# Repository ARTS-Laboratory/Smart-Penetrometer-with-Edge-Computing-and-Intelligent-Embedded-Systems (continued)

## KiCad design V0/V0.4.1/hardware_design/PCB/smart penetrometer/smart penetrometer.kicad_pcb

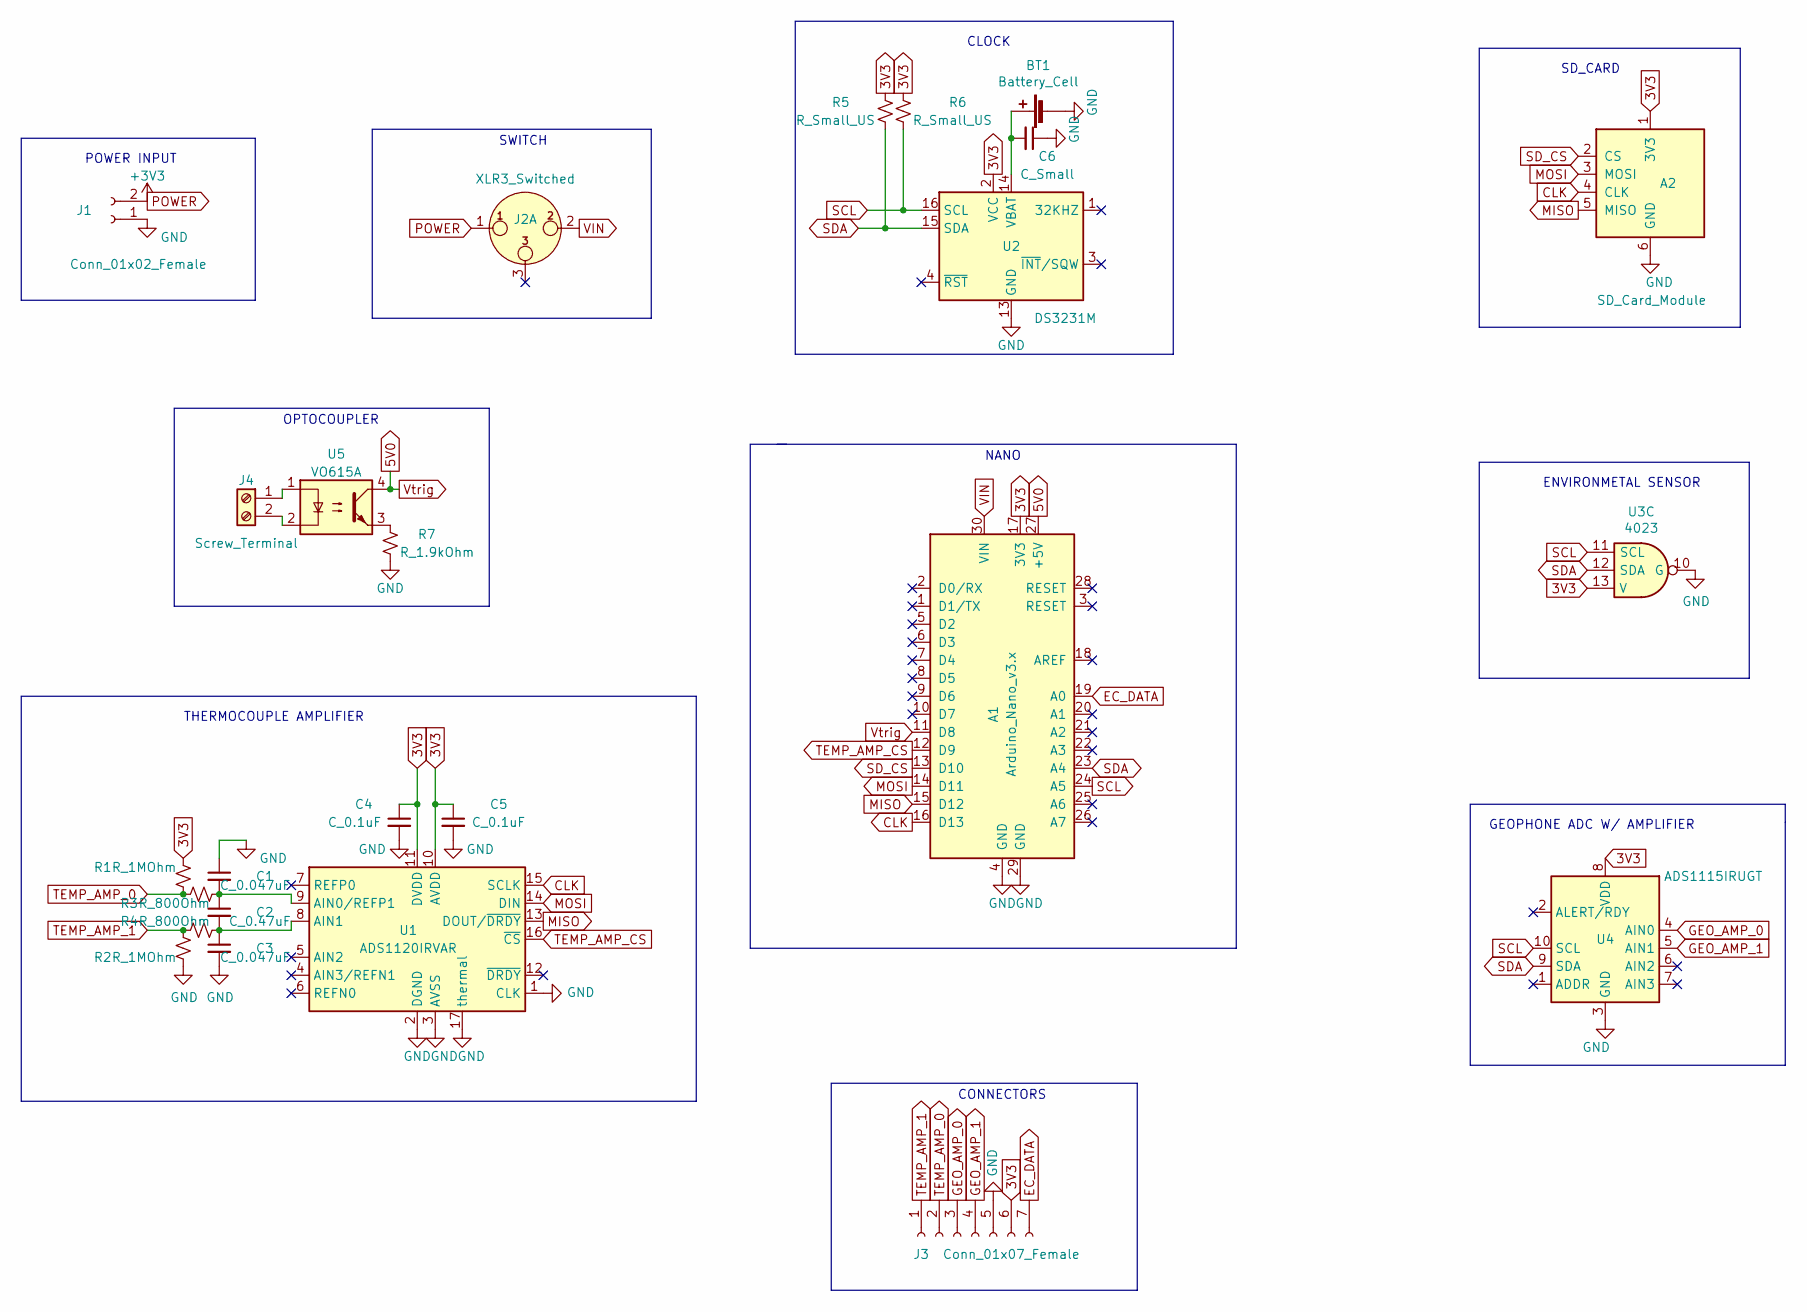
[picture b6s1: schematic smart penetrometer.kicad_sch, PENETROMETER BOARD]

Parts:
A1: Arduino_Nano_v3.x; Arduino_Nano
A2: SD_Card_Module; SD Module
BT1: Battery_Cell; battery_holder_10mm
C1, C3: C_0.047uF; C_1206_3216Metric
C2: C_0.47uF; C_1206_3216Metric
C4, C5: C_0.1uF; C_1206_3216Metric
C6: C_Small; C_1206_3216Metric
J1: Conn_01x02_Female; PinSocket_1x02_P2.54mm_Horizontal
J2: XLR3_Switched; grounded_switch
J3: Conn_01x07_Female; PinSocket_1x07_P2.54mm_Horizontal
J4: Screw_Terminal; TerminalBlock_bornier-2_P5.08mm
R1, R2: R_1MOhm; R_1206_3216Metric
R3, R4: R_800Ohm; R_1206_3216Metric
R5, R6: R_Small_US; R_1206_3216Metric
R7: R_1.9kOhm; R_1206_3216Metric
U1: ADS1120IRVAR; VQFN-16-1EP_3x3mm_P0.5mm_EP1.45x1.45mm_ThermalVias
U2: DS3231M; SOIC-16W_7.5x10.3mm_P1.27mm
U3: 4023; TDS_module
U4: ADS1115IRUGT; 10X2QFN
U5: VO615A; Vishay_VOS615A

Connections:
3V3: A1.17 (3V3), A2.1 (3V3), C4.1, C5.1, J3.6, R1.1, R5.1, R6.1, U1.10 (AVDD), U1.11 (DVDD), U2.2 (VCC), U3.13, U4.8 (VDD)
5V0: A1.11 (D8), A1.27 (+5V), U5.4
CLK: A1.16 (D13), A2.4 (CLK), U1.15 (SCLK)
EC_DATA: A1.19 (A0), J3.7
GEO_AMP_0: J3.3, U4.4 (AIN0)
GEO_AMP_1: J3.4, U4.5 (AIN1)
GND: A1.4 (GND), A1.29 (GND), A2.6 (GND), BT1.2 (-), C1.1, C3.2, C4.2, C5.2, C6.1, J1.1, J3.5, R2.2, R7.2, U1.1 (CLK), U1.2 (DGND), U1.3 (AVSS), U1.17 (thermal), U2.5 (GND), U2.6 (GND), U2.7 (GND), U2.8 (GND), U2.9 (GND), U2.10 (GND), U2.11 (GND), U2.12 (GND), U2.13 (GND), U3.10, U4.3 (GND)
MISO: A1.15 (D12), A2.5 (MISO), U1.13 (DOUT/~DRDY)
MOSI: A1.14 (D11), A2.3 (MOSI), U1.14 (DIN)
unnamed: BT1.1 (+), C6.2, U2.14 (VBAT)
unnamed: C1.2, C2.1, R3.1, U1.9 (AIN0/REFP1)
unnamed: C2.2, C3.1, R4.1, U1.8 (AIN1)
unnamed: J4.1, U5.1
unnamed: J4.2, U5.2
unnamed: R7.1, U5.3
POWER: J1.2, J2.1
SCL: A1.24 (A5), R6.2, U2.16 (SCL), U3.11, U4.10 (SCL)
SDA: A1.23 (A4), R5.2, U2.15 (SDA), U3.12, U4.9 (SDA)
SD_CS: A1.13 (D10), A2.2 (CS)
TEMP_AMP_0: J3.2, R1.2, R3.2
TEMP_AMP_1: J3.1, R2.1, R4.2
TEMP_AMP_CS: A1.12 (D9), U1.16 (~CS)
VIN: A1.30 (VIN), J2.2

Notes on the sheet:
THERMOCOUPLE AMPLIFIER
POWER INPUT
NANO
SWITCH
CLOCK
CONNECTORS
SD_CARD
ENVIRONMETAL SENSOR
GEOPHONE ADC W/ AMPLIFIER
OPTOCOUPLER

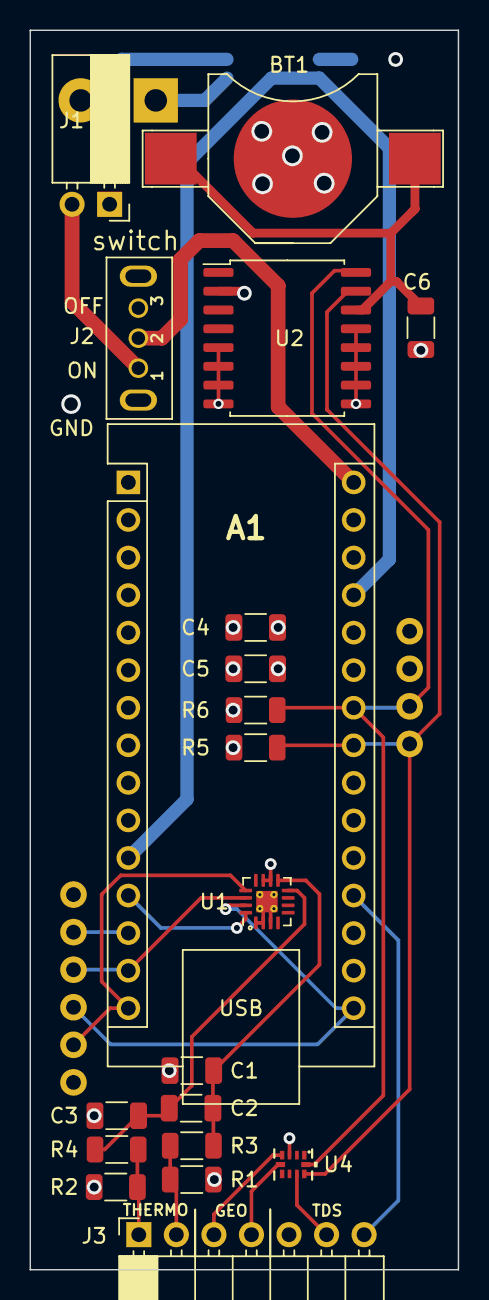
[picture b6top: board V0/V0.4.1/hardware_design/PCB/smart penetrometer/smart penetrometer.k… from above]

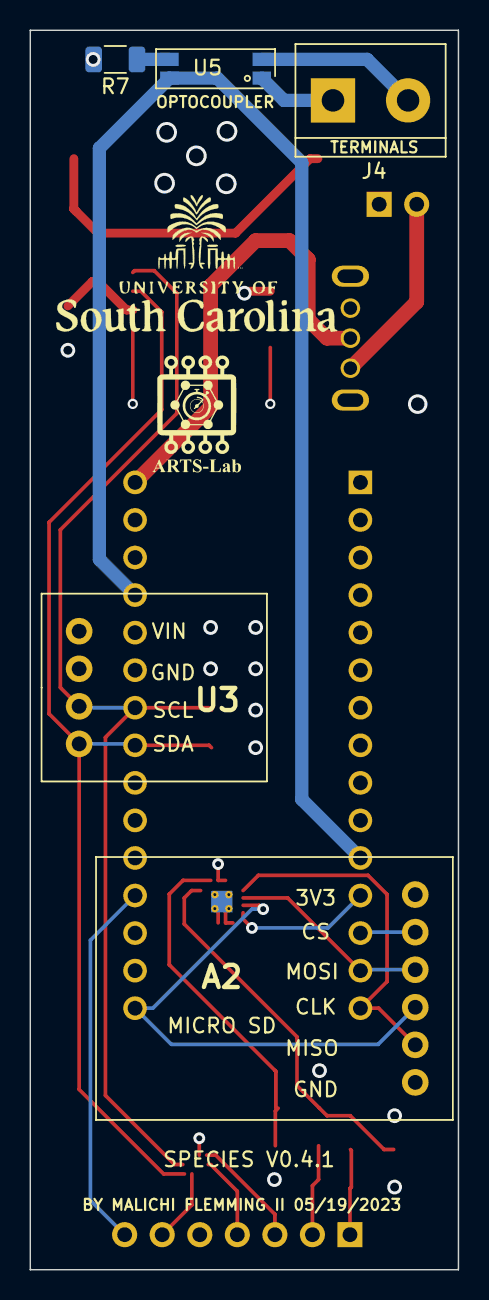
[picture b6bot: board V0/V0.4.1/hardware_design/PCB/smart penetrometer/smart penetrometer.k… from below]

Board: 4 copper layers, 29.0 x 83.8 mm, 25 parts (5 on the bottom side), 23 nets.

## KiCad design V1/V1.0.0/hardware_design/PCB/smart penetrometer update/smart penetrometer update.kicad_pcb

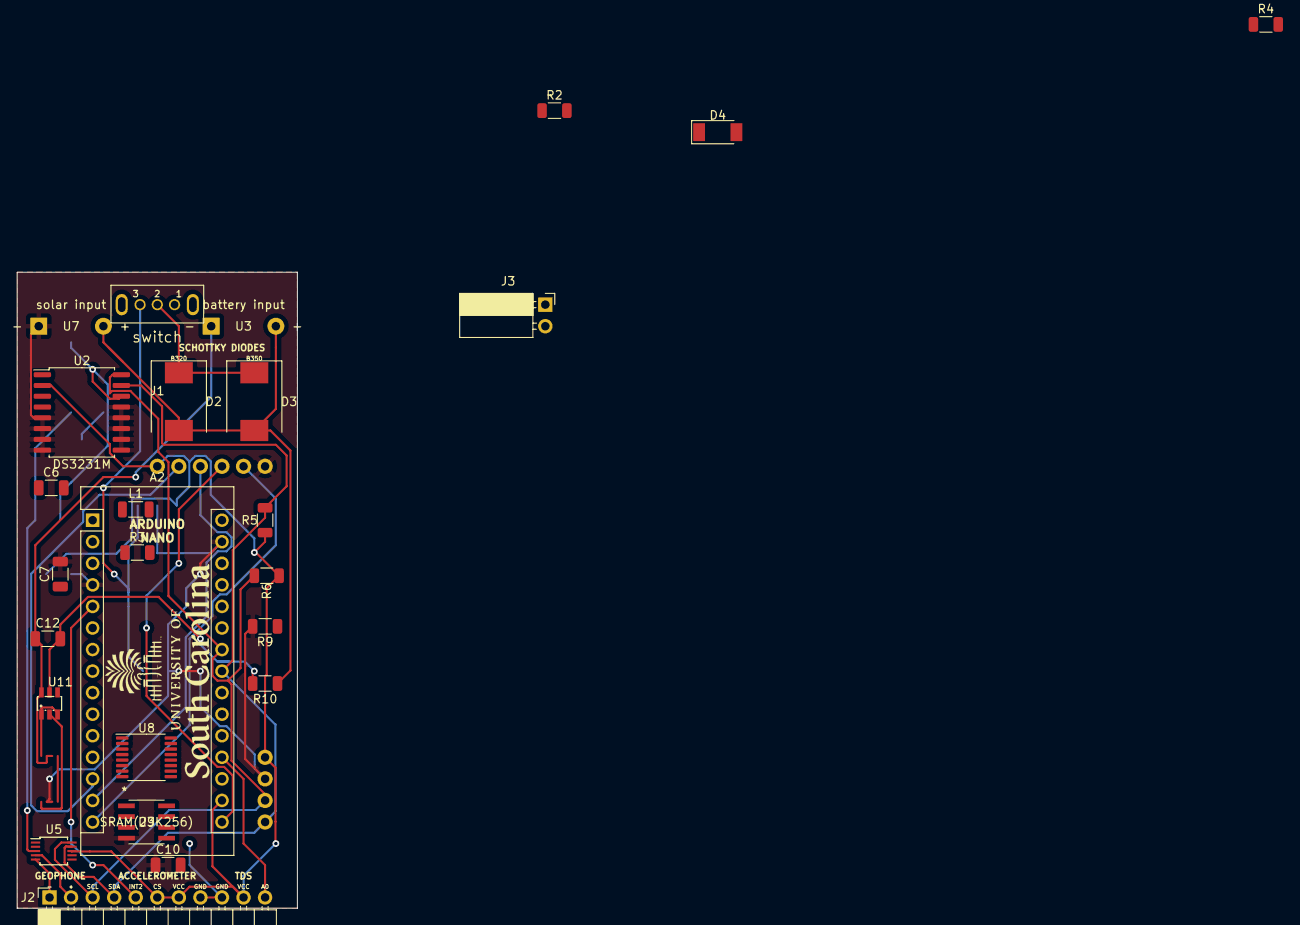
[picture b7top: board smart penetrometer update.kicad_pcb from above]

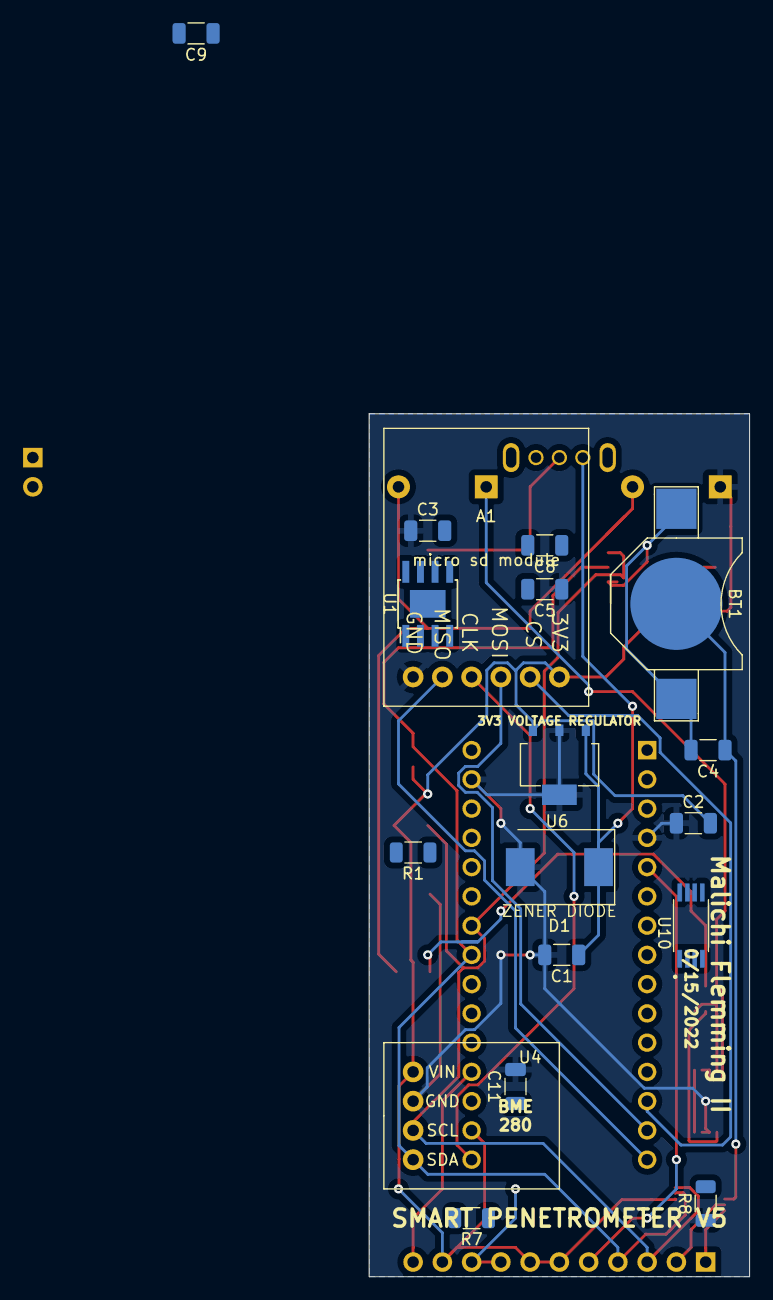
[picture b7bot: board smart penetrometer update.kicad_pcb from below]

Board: 2 copper layers, 33.0 x 74.9 mm, 45 parts (18 on the bottom side), 35 nets.

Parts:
A1: SD_Card_Module; SD Module
A2: Arduino_Nano_v3.x; Arduino_Nano
BT1: Battery_Cell; battery_holder_10mm
C1, C9, C10, C11: C_0.1uF; C_1206_3216Metric
C2, C3, C8: C_10uF; C_1206_3216Metric
C4: C_Small; C_1206_3216Metric
C5, C7: C_0.047uF; C_1206_3216Metric
C6: C_0.47uF; C_1206_3216Metric
C12: CP1_Small; C_1206_3216Metric
D1: D_Zener_Small; D_SMC
D2: B320; D_SMC
D3: B350; D_SMC
D4: PMEG6045ETP; D_SOD-128
J1: XLR3_Switched; grounded_switch
J2: Conn_01x11_Female; PinSocket_1x11_P2.54mm_Horizontal
J3: Conn_01x02_Female; PinSocket_1x02_P2.54mm_Horizontal
L1: L; L_1206_3216Metric
R1, R2: R_1MOhm; R_1206_3216Metric
R3, R4: R_800Ohm; R_1206_3216Metric
R5, R6, R7, R8, R9, R10: R_Small_US; R_1206_3216Metric
U1: 4001; uofsc_logo_1in
U1#2: LM22676MR-5; TI_SO-PowerPAD-8
U2: DS3231M; SOIC-16W_7.5x10.3mm_P1.27mm
U3: Battery_Input
U4: 4023; TDS_module
U5: ADS1115IDGS; TSSOP-10_3x3mm_P0.5mm
U6: 3v3_Voltage_Regulator; BD433M2FP3_CE2
U7: Solar_Input; Battery_Input
U8: ADS1120-PW; TSSOP-16_4.4x5mm_P0.65mm
U9: SRAM(23K256); 23K256T-E&slash_SN
U10: FS8205A; DUAL_MOSFET(FS8205A)
U11: DW01; BATTERY_PROTECTION_IC(DW01A)

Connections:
+BATT: D2.2, D3.2, R10.1, U3.1, U7.1
-BATT: C12.1, U3.2, U10.2, U10.3, U11.6
GND: A1.6, A2.4, A2.29, C1.2, C2.1, C3.1, C5.1, C7.2, C9.2, C10.1, C11.2, D1.2, D4.2, R2.2, R8.1, R9.2, U1#2.6, U2.5, U2.6, U2.7, U2.8, U2.9, U2.10, U2.11, U2.12, U2.13, U4.10, U6.2, U6.4, U7.2, U8.3, U8.5, U9.4, U10.6, U10.7
GNDREF: J2.8, J2.9
GNDS: BT1.2, C4.1, U5.3
unnamed: A1.1, A2.30, C2.2, C9.1, C11.1, J2.6, J2.7, J2.10, R1.1, R5.1, R6.1, U2.2, U4.13, U5.8, U6.3, U8.12, U8.13, U9.8
unnamed: A1.2, A2.13
unnamed: A1.3, A2.14, U8.16, U9.5
unnamed: A1.4, A2.16, U8.1, U9.6
unnamed: A1.5, A2.15, U8.15, U9.2
unnamed: A2.5, J2.5
unnamed: A2.10, U9.7
unnamed: A2.11, U9.1
unnamed: A2.12, U8.2
unnamed: A2.19, J2.11
unnamed: A2.23, J2.4, R5.2, U2.15, U4.12, U5.9
unnamed: A2.24, J2.3, R6.2, U2.16, U4.11, U5.10
unnamed: BT1.1, C4.2, U2.14
unnamed: C1.1, C10.2, D1.1, L1.1, R7.1, U6.1
unnamed: C3.2, J1.3, U1#2.7
unnamed: C5.2, C6.1, R3.1, U8.11
unnamed: C6.2, C7.1, R4.1, U8.10
unnamed: C8.1, D4.1, L1.2, U1#2.8
unnamed: C8.2, U1#2.1
unnamed: C12.2, R10.2, U11.5
unnamed: D2.1, D3.1, J1.2
unnamed: J2.1, U5.5
unnamed: J2.2, U5.4
unnamed: J3.1, R2.1, R4.2
unnamed: J3.2, R1.2, R3.2
unnamed: R7.2, R8.2, U1#2.4
unnamed: R9.1, U11.2
unnamed: U10.1, U10.8
unnamed: U10.4, U11.1
unnamed: U10.5, U11.3

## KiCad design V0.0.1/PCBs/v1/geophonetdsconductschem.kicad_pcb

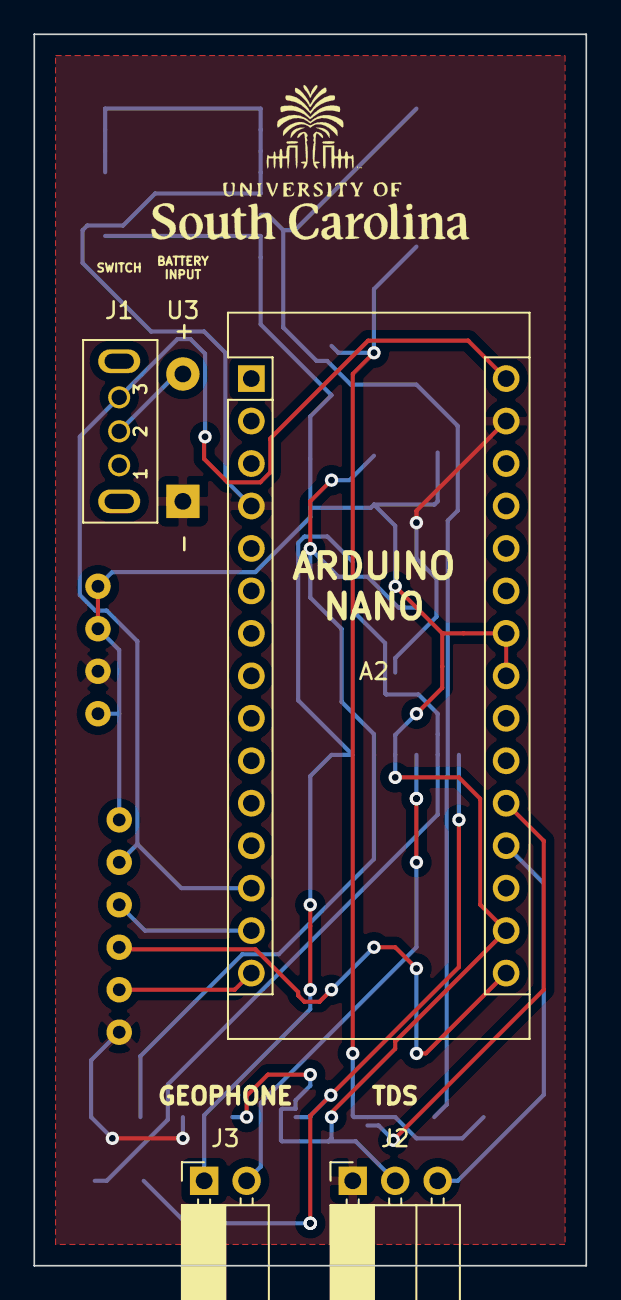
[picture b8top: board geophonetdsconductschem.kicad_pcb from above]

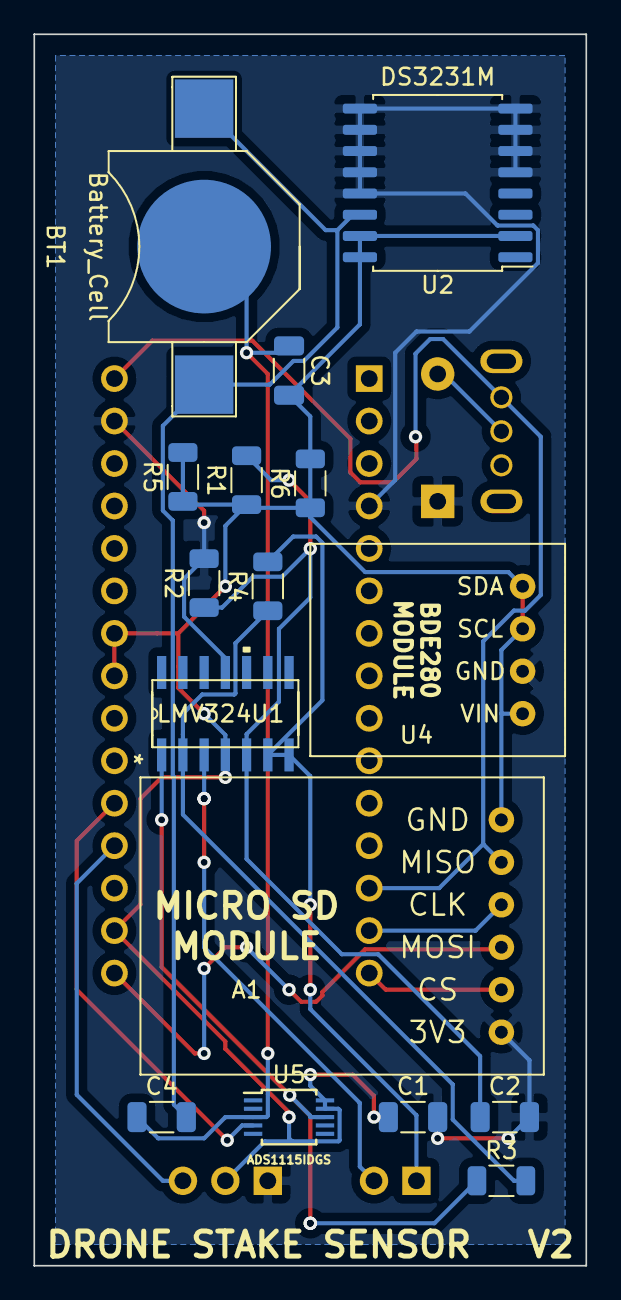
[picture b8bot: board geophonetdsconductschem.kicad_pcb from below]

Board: 2 copper layers, 33.0 x 73.7 mm, 21 parts (16 on the bottom side), 16 nets.

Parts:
A1: SD_Card_Module; SD Module
A2: Arduino_Nano_v3.x; Arduino_Nano
BT1: Battery_Cell; battery_holder_10mm
C1, C2, C3, C4: C_Small; C_1206_3216Metric
J1: XLR3_Switched; grounded_switch
J2: Conn_01x03_Female; PinSocket_1x03_P2.54mm_Horizontal
J3: Conn_01x02_Female; PinSocket_1x02_P2.54mm_Horizontal
R1, R2, R3, R4, R5, R6: R_Small_US; R_1206_3216Metric
U1: LMV324; LMV324IDR
U2: DS3231M; SOIC-16W_7.5x10.3mm_P1.27mm
U3: Battery_Input
U4: 4023; TDS_module
U5: ADS1115IDGS; TSSOP-10_3x3mm_P0.5mm

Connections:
GND: A1.6, A2.4, A2.29, C1.2, C2.2, J2.1, R2.2, U1.11, U2.5, U2.6, U2.7, U2.8, U2.9, U2.10, U2.11, U2.12, U2.13, U3.2, U4.10
GNDS: BT1.2, C3.1, C4.1, U5.3
unnamed: A1.1, A2.17, A2.23, A2.24, C1.1, C3.2, J2.2, R1.1, R5.1, R5.2, R6.1, R6.2, U1.4, U2.2, U2.15, U2.16, U4.11, U4.12, U4.13, U5.9, U5.10
unnamed: A1.2, A2.13, A2.30, J1.3
unnamed: A1.3, A2.14
unnamed: A1.4, A2.16
unnamed: A1.5, A2.15
unnamed: A2.19, J2.3
unnamed: A2.20, U5.4
unnamed: BT1.1, C4.2, U2.14
unnamed: C2.1, R1.2, R2.1, U1.5
unnamed: J3.1, R4.2, U1.6, U1.7
unnamed: J3.2, U1.3
unnamed: R3.1, U1.1, U5.8
unnamed: R3.2, R4.1, U1.2
VCC: J1.2, U3.1

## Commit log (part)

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2022-04-25 malichi update
2022-04-25 Rename Readme to README.md
2022-04-26 cleaned up papers
2022-05-05 malichi updates
2022-07-01 repository reorganization
2022-07-04 added markdown files
2022-07-12 code update
2022-07-26 schematic update
2022-07-28 SCHEMATIC UPDAYE
2022-11-12 no change
2023-04-07 Fix PCB Design
    Several traces missing in PCB Design.
2023-04-07 moved v1 to v0.4.0
2023-04-07 added notes on versions.
2023-04-10 Edited V0.4.0 to add CAD and Code folders and files
    Added CAD and code folders with files for editing in V0.4.0, and deleted unnecessary files in the PCB folder
2023-05-19 modified the CAD model for the geophone
2023-05-19 cleaned up v0.4.0 and added some tasks
2023-05-19 small updates
2023-05-19 added 0.4.1
2023-05-19 pcb update
2023-05-19 removed backups and added logo
2023-05-19 PCB V0.4.1 UPDATE
2023-05-20 added new icon with text
2023-06-24 new branch for wireless created
2023-06-24 cleaned the branch
2023-06-24 added single nodal testing code
2023-07-09 transmit and receive work
2023-07-09 arduino transmitter code
2023-07-09 Multinodal code added
2023-07-09 Arduino nodes code
2023-07-11 update to reade the pipe
2023-07-12 multiple clients pipeline setup
2023-07-12 rf24_network python implementation
2023-07-13 The network has a loss detection system
2023-07-14 reorganized structure
2023-07-14 CAD update
2023-07-17 pcb and cad update
2023-07-28 v5 update
2023-07-31 Update rf24_network.ino
    Writes data to sensor.csv file
2023-10-13 added conductivity penetrometer version
2023-11-27 reorganized folders
2023-11-27 rename files
2023-11-27 updated source code
2023-11-27 readme updates
2023-11-28 added BOM
2024-01-29 version 5.2 upload
2024-02-24 wireless communication update
2024-03-01 Code used for flume test
2024-03-01 Code for flume test
2024-03-01 Flume test data results
2024-03-02 cleaned up Wireless_Conductivity code and removed receiver code
2024-04-02 V0.6.0 release
2024-04-02 correction
2024-04-03 V0.6.0 CAD upload
2024-04-06 version 0.6.0 update
2024-04-06 Added potential system development layout
2024-04-07 removed version numbers from systems
2024-04-08 created the Columbia folder
2024-04-08 spike-only code
2024-04-09 Added Missouri content.
2024-04-09 test to see if figures are linked from main page
2024-04-09 fixing image links
2024-04-09 removing extra figures
2024-04-15 Mississippi v0.1
2024-07-13 cleaned up repo readmes
2024-07-19 software update
2024-08-06 updated code
    Specified decimal points in receiver code. Updated TDS function: changed voltage from 3.6 to 3.2 to reflect the V0.6.0 PCBs and changed the print value to be voltage and not PPM.
2024-09-14 Created spot for base station files
    Kicad for receiver PCB in base station
2025-01-03 updated base station receiver pcb
    decreased board size, flipped nRF pinout, and added clearer silkscreen labels
2025-01-03 grounded mounting holes
2025-01-03 removed lock and cache files
2025-01-03 updated gitignore to not take .lck and cache files
2025-01-03 update readme
    describe base station folder as well as clarify apparent "loose connections" on the pcb file
2025-01-03 update readme
    more descriptive note
2025-01-24 added QR code
2025-02-06 Create raspberry_pi
2025-02-22 folder name update
2025-02-22 file name update
2025-03-24 6.1 update
2025-05-15 V0.6.1 update
2025-05-16 V0.6.2 update
2025-05-18 V0.6.2 CAD update
2025-05-21 downsizing folder names
2025-05-22 cad model update
2025-05-26 V0.6.2 node software update
2025-05-26 updated receiver software
2025-07-14 updated two errors on PCB
2025-09-19 created v0.7
2025-09-22 updated BOM
2025-10-03 updated outer tube
2025-11-05 Create BOM-SPECIES-Columbia-v0.6.2.xlsx
    uploaded base station components
2026-01-06 added cap cad file
2026-01-06 added screw holes to cap cad
2026-01-06 completed cap cad
2026-01-06 uploaded cap stl
2026-01-07 v2 of cap 0.7.0 added
2026-01-08 revised sizing errors in cap2
2026-01-13 uploaded new cap design (3)
2026-01-23 0.7.0 updated body and base
2026-01-23 stls and changed names
2026-01-26 minor updates to base
2026-01-26 labeling changes
2026-01-27 changed minor dimension
2026-01-27 wrong again so minor sizing update
2026-02-03 organizing
2026-02-04 update solar cap
2026-02-04 uploaded most recent cap
2026-03-22 version 6.3 added
2026-05-29 editing bom
2026-05-29 reduced rod to 36 in for free shipping
2026-06-17 add README.md
2026-06-25 sensor software update
